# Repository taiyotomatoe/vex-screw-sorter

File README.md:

# Automatic Screw Sorter for VEX Robotics
**An automatic screw sorter, designed for standard VEX screws of sizes 0.25" up to 2.00".**  
*Note: Other screws such as shoulder screws may not work.*

We all hate having to sort our screws manually, and no one puts the screws back in the right place. 

That's why I made this screw sorter, which works **without requiring a human operator** to manually place screws on the sorter - just dump your screws in the box, start the motor, and get it sorted automatically.

### Preview: 

### Features:
- Knob, to control the motor speed
- LCD Screen to display current speed + number 

# Make your own sorter! 
All files needed to build this project are provided in their respective folders. 

### PCB: 
(Kicanvas wouldn't work...) Routing is a bit of a mess. (I'm a noobie at this)

### Firmware: 
Arduinon code

### Bill of Materials
[Link](https://docs.google.com/spreadsheets/d/1GzJbDsBg9s3fJ3GwzlsMUPDhf9ZihwElanYWZgdYd-w/edit?usp=sharing)

- XL4015 DCDC step-down converter
- JGA25-370 DC Reduction Motor with Encoder - 12V, 280RPM
- LCD Blue Screen IIC/I2C 2004 5V LCD Module for Arduino
- Alps EC11E Rotary Encoder
- Arduino Nano Every
- Male to Female Jumper Wire
- 2pcs 902540 3.7V Battery LIPO Lipo Battery 800mAh Battery
- 1.25T-2A: Connector for Lipo Battery
- WAFER-PH2.0-6PWB
- 2.54 Pitch PIn sockets 
- Magnets 5-pack

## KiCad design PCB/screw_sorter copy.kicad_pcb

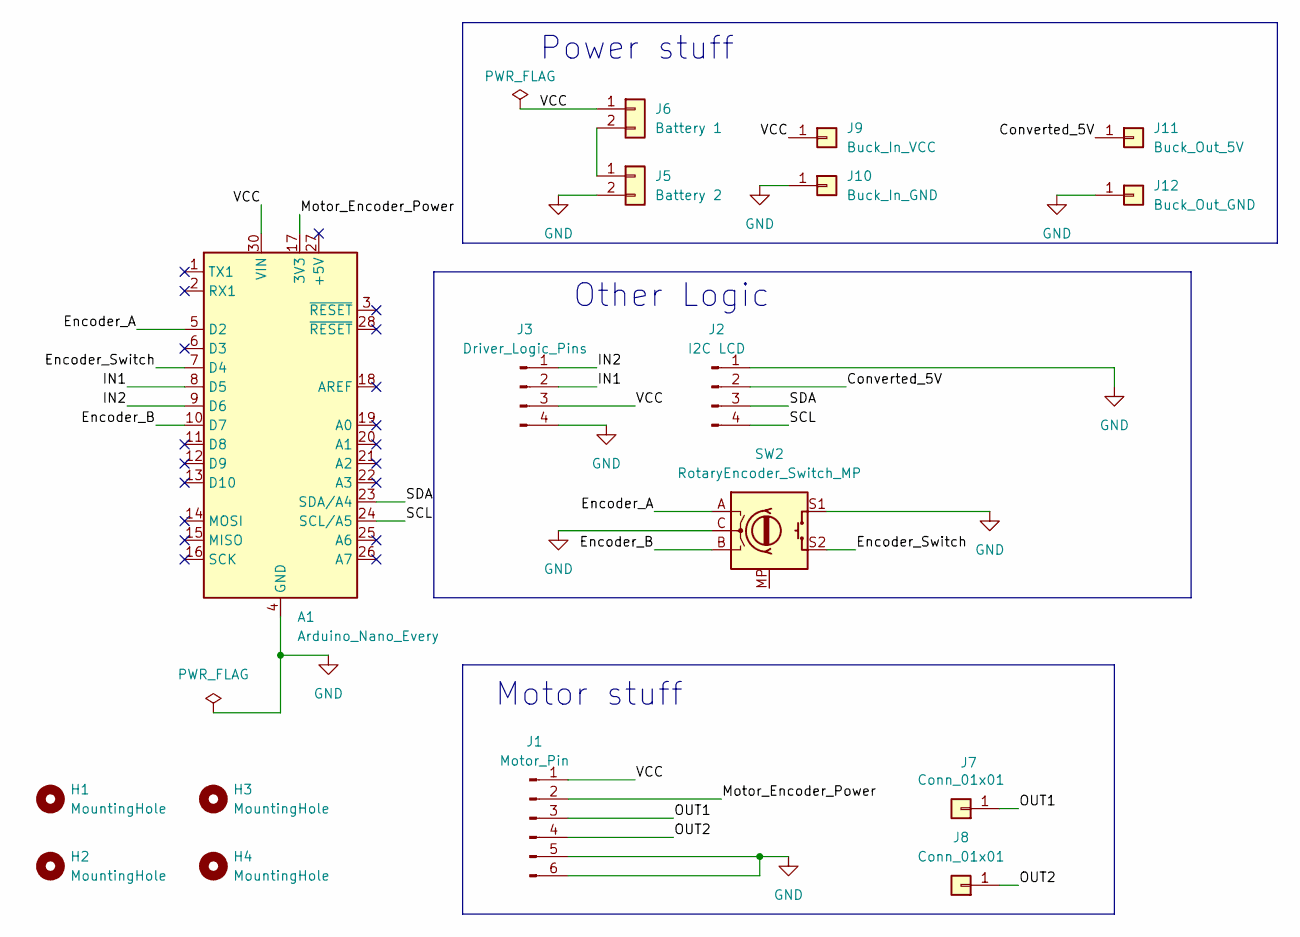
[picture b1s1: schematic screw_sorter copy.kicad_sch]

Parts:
A1: Arduino_Nano_Every; Arduino_Nano
H1, H2, H3, H4: MountingHole; MountingHole_3.2mm_M3
J1: Motor_Pin; WAFER-PH2_0-6PWB
J2: I2C LCD; PinSocket_1x04_P2.54mm_Vertical
J3: Driver_Logic_Pins; PinHeader_1x04_P2.54mm_Vertical
J5: Battery 2; 1_25T-1-2A
J6: Battery 1; 1_25T-1-2A
J7, J8: Conn_01x01; PinHeader_1x01_P2.54mm_Vertical
J9: Buck_In_VCC; PinHeader_1x01_P2.54mm_Vertical
J10: Buck_In_GND; PinHeader_1x01_P2.54mm_Vertical
J11: Buck_Out_5V; PinHeader_1x01_P2.54mm_Vertical
J12: Buck_Out_GND; PinHeader_1x01_P2.54mm_Vertical
SW2: RotaryEncoder_Switch_MP; RotaryEncoder_Alps_EC11E-Switch_Vertical_H20mm_CircularMoun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

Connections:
/Converted_5V: J2.2, J11.1 (Pin_1_1)
/Encoder_A: A1.5 (D2), SW2.A
/Encoder_B: A1.10 (D7), SW2.B
/Encoder_Switch: A1.7 (D4), SW2.S2
/IN1: A1.8 (D5), J3.2
/IN2: A1.9 (D6), J3.1
/Motor_Encoder_Power: A1.17 (3V3), J1.2
/OUT1: J1.3, J7.1 (Pin_1_1)
/OUT2: J1.4, J8.1 (Pin_1_1)
/SCL: A1.24 (SCL/A5), J2.4
/SDA: A1.23 (SDA/A4), J2.3
/VCC: A1.30 (VIN), J1.1, J3.3, J6.1, J9.1 (Pin_1_1)
GND: A1.4 (GND), A1.29 (GND), J1.5, J1.6, J2.1, J3.4, J5.2, J10.1 (Pin_1_1), J12.1 (Pin_1_1), SW2.C, SW2.S1
unnamed: J5.1, J6.2

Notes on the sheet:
Motor stuff
Power stuff
Other Logic

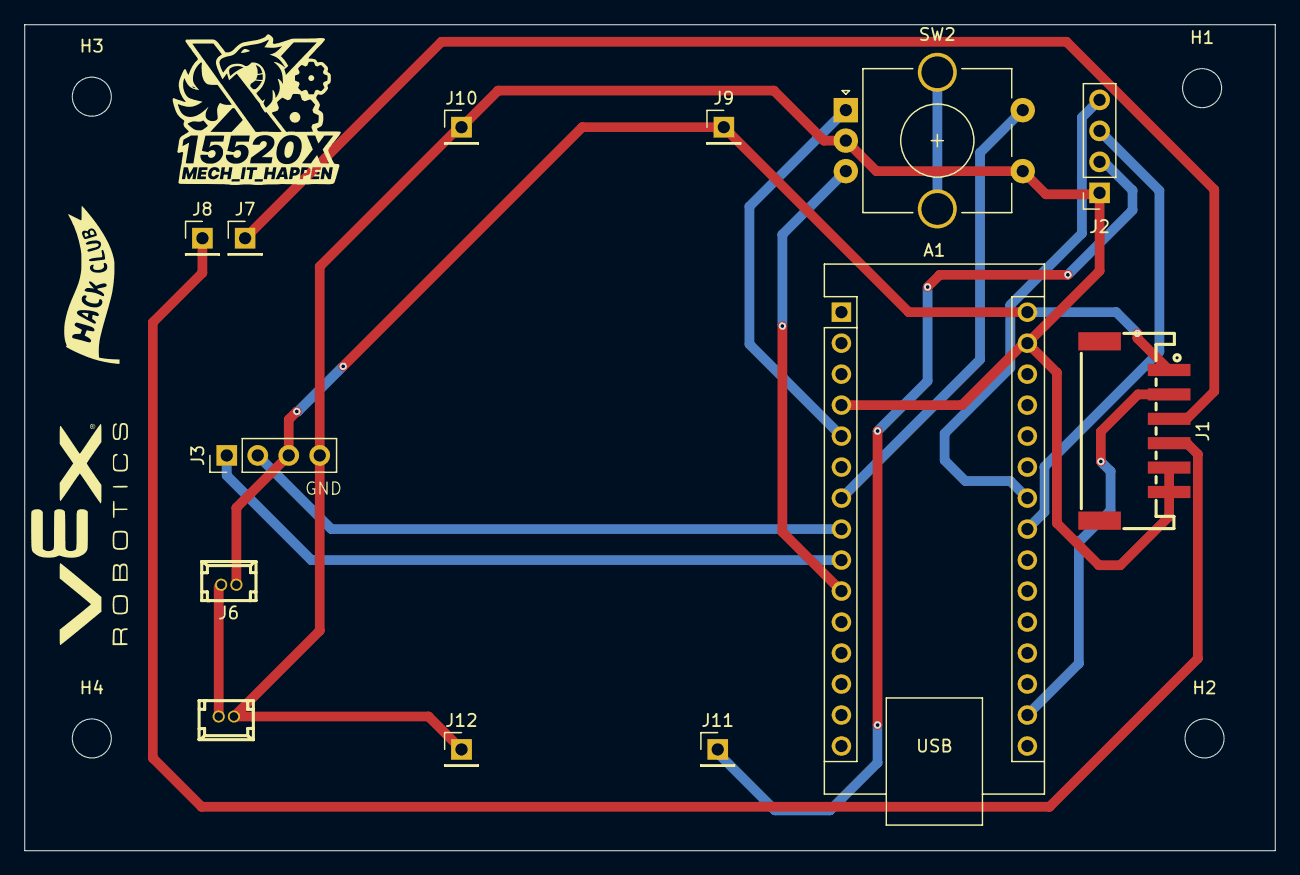
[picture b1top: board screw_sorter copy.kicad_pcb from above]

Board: 2 copper layers, 102.5 x 67.7 mm, 17 parts (0 on the bottom side), 14 nets.
